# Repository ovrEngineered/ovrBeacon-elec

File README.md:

# ovrBeacon-elec

This project contains an open-source implementation of a Bluetooth Low Energy sensor beacon.
The beacon has the following features:
 - Integrated temperature sensor
 - Integrated light sensor
 - Integrated accelerometer
 - Remotely controlled LEDs
 - Wireless charging via Qi standard
 
Note: this repository contains the schematics and PCB design. The firmware repository is located [here](https://github.com/ovrEngineered/ovrBeacon-fw).

## Physical Description

| Height       | Width        | Depth w/ programming header | Depth w/o programming header |
| ------------ | ------------ | --------------------------- | ---------------------------- |
| 1.85" (47mm) | 1.06" (27mm) | 0.57" (14.48mm)             | 0.41" (10.41mm)              |

## Parameters
| Parameter               | Min  | Typical | Max    | Units |
| ----------------------- | ---- | ------- | ------ | ----- |
| Temperature accuracy**  | -    | +/- 1   | -      | °C    |
| Acceleration range      | -16  | -       | +16    | g     |
| Acceleration resolution | -    | 4       | -      | mg    |
| Light sensitivity       | 0.01 | -       | 64,000 | lux   |
| Battery Capacity***     | -    | 500     | -      | mAh.  |
** accuracy can be increased with pin-compatible parts 

*** capacity can be increased with replacement batteries

## Links
 * [Schematic PDF](output/ovrBeacon_schematic.pdf)
 * [PCB Layout PDF](output/ovrBeacon_layout.pdf)

## Built With
 * [KiCad](http://kicad-pcb.org/)

## Versioning
We use [SemVer](http://semver.org/) for versioning. For the versions available, see the [tags on this repository](https://github.com/ovrEngineered/ovrBeacon-elec/tags). 

## License
This project is licensed under the MIT License:

> Permission is hereby granted, free of charge, to any person obtaining a copy of this software and associated documentation files (the "Software"), to deal in the Software without restriction, including without limitation the rights to use, copy, modify, merge, publish, distribute, sublicense, and/or sell copies of the Software, and to permit persons to whom the Software is furnished to do so, subject to the following conditions:
>
> The above copyright notice and this permission notice shall be included in all copies or substantial portions of the Software.
>
> THE SOFTWARE IS PROVIDED "AS IS", WITHOUT WARRANTY OF ANY KIND, EXPRESS OR IMPLIED, INCLUDING BUT NOT LIMITED TO THE WARRANTIES OF MERCHANTABILITY, FITNESS FOR A PARTICULAR PURPOSE AND NONINFRINGEMENT. IN NO EVENT SHALL THE AUTHORS OR COPYRIGHT HOLDERS BE LIABLE FOR ANY CLAIM, DAMAGES OR OTHER LIABILITY, WHETHER IN AN ACTION OF CONTRACT, TORT OR OTHERWISE, ARISING FROM, OUT OF OR IN CONNECTION WITH THE SOFTWARE OR THE USE OR OTHER DEALINGS IN THE SOFTWARE.

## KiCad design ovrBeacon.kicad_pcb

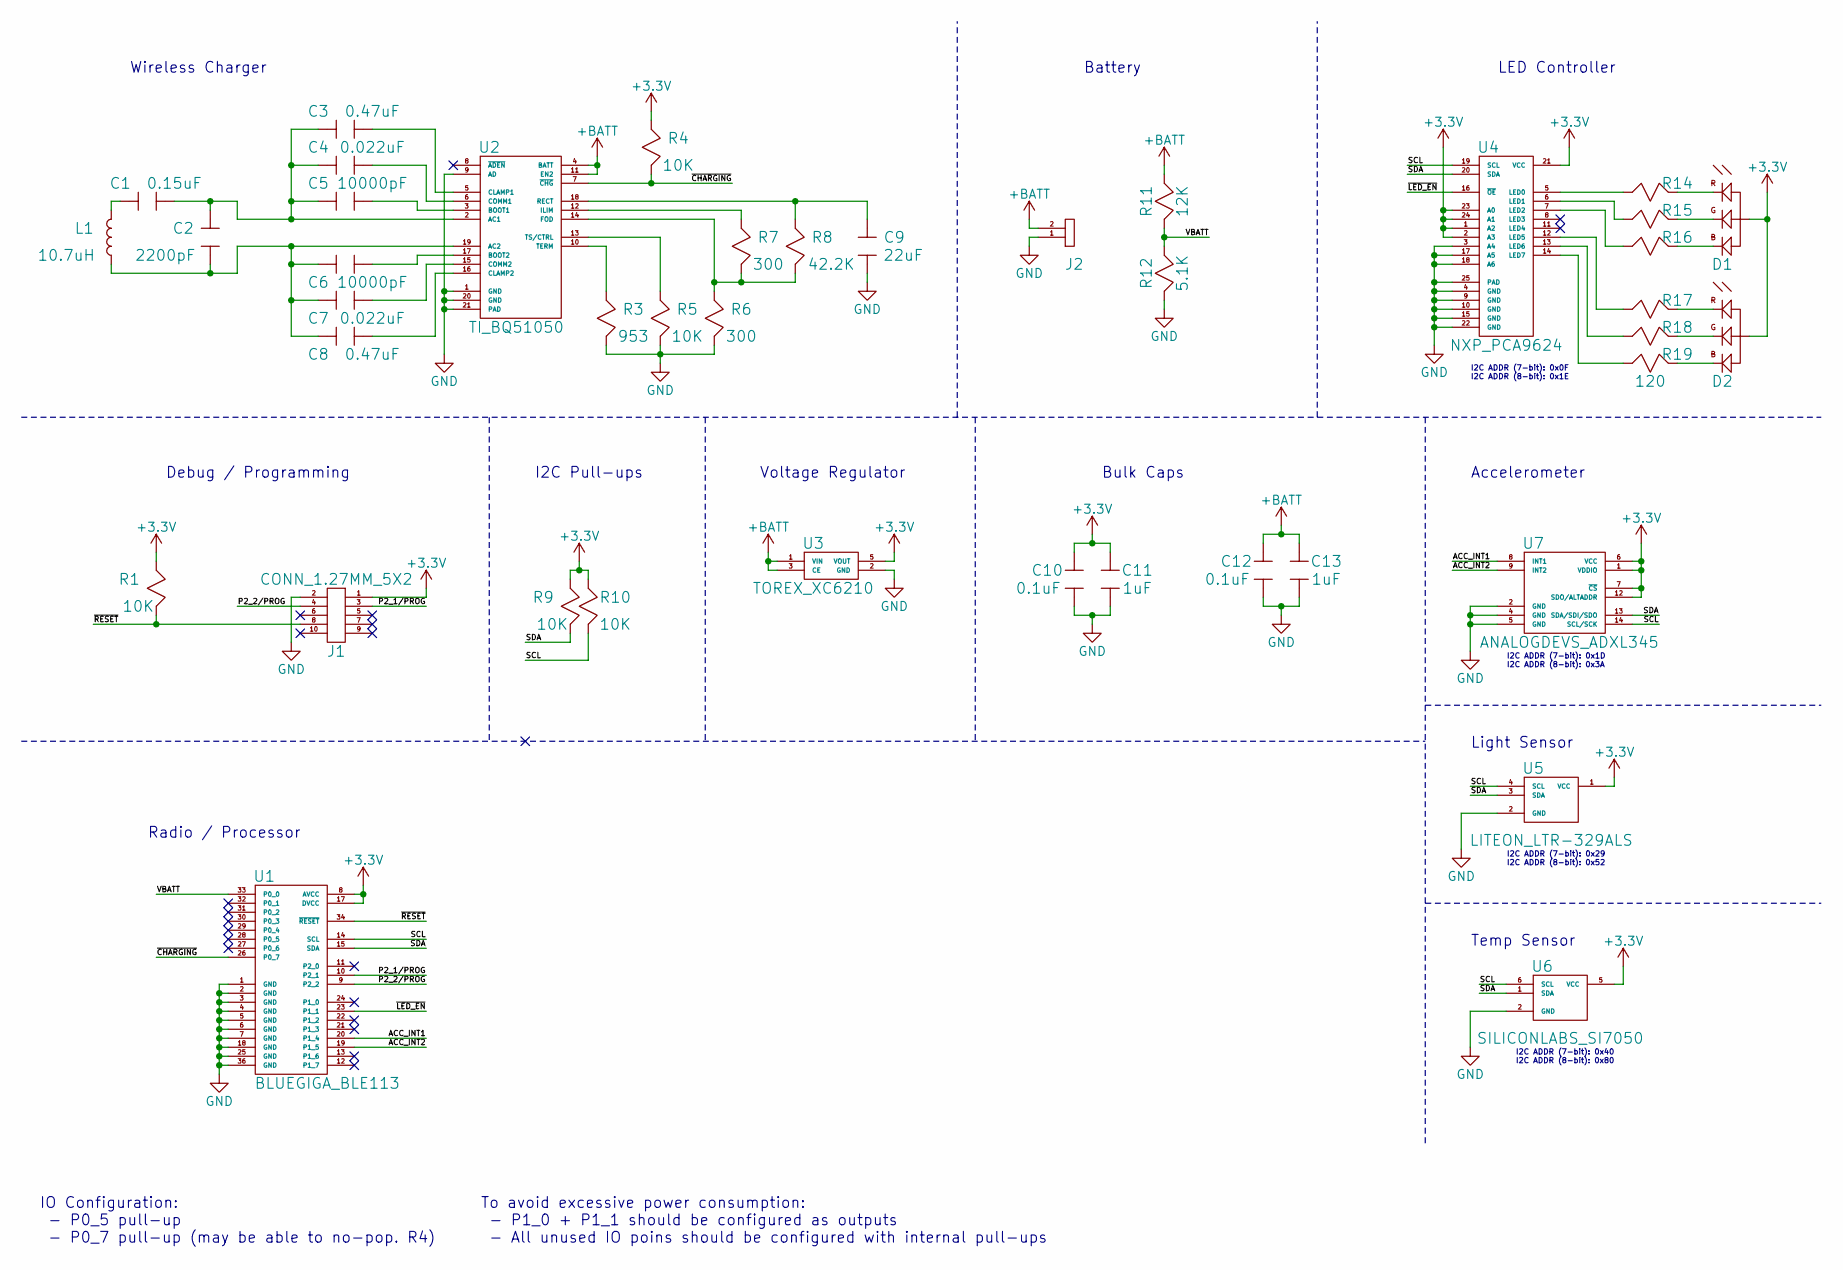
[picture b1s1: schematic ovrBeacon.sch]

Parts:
C1: C_0.15uF_25v_0603; C_0603; Man. Part Num. C1608X7R1E154K080AA
C2: C_2200pF_50v_0603; C_0603; Man. Part Num. GRM188R71H222KA01D
C3, C8: C_0.47uF_25v_0603; C_0603; Man. Part Num. C1608X5R1E474K080AC
C4, C7: C_0.022uF_25v_0603; C_0603; Man. Part Num. GRM188R71E223KA01D
C5, C6: C_10000pF_25v_0603; C_0603; Man. Part Num. GRM188R71E103KA01D
C9: C_22uF_25v_0805; C_0805; Man. Part Num. GRT21BR61E226ME13L
C10, C12: C_0.1uF_10v_0603; C_0603; Man. Part Num. GRM188R71C104KA01D
C11, C13: C_1uF_10v_0805; C_0805; Man. Part Num. GRM21BR71A105KA01L
D1, D2: CREE_CLV1A_FKB; Man. Part Num. CLV1A-FKB-CK1N1G1BB7R4S3
J1: CONN_1.27MM_5X2; 20021111-00010T4LF; Man. Part Num. 20021111-00010T4LF
J2: CONN_2MM_2; SIP_2MM_2; Man. Part Num. 951102-8622-AR
L1: QIRX_10.7uH; SIP_2MM_2; Man. Part Num. IWAS3827ECEB100J50
R1, R4, R5, R9, R10: R_10K_1%_0603; R_0603; Man. Part Num. CRCW060310K0FKEA
R3: R_953_1%_0603; R_0603; Man. Part Num. RC0603FR-07953RL
R6, R7: R_300_1%_0603; R_0603; Man. Part Num. RC0603FR-07300RL
R8: R_42.2K_1%_0603; R_0603; Man. Part Num. RC0603FR-0742K2L
R11: R_12K_1%_0603; R_0603; Man. Part Num. CRCW060312K0FKEA
R12: R_5.1K_1%_0603; R_0603; Man. Part Num. CRCW06035K10FKEA
R14, R15, R16, R17, R18, R19: R_120_1%_0603; R_0603; Man. Part Num. CRCW0603120RFKEA
U1: BLUEGIGA_BLE113; BLE113; Man. Part Num. BLE113-A-M256K
U2: TI_BQ51050; Man. Part Num. BQ51050BRHLR
U3: TOREX_XC6210; SOT-25-5; Man. Part Num. XC6210B332MR-G
U4: NXP_PCA9624; Man. Part Num. PCA9624BS,118
U5: LITEON_LTR-329ALS; Man. Part Num. LTR-329ALS-01
U6: SILICONLABS_SI7050; Man. Part Num. SI7050-A20-IM
U7: ANALOGDEVS_ADXL345; Man. Part Num. ADXL345BCCZ-RL

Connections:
+3V3: C10.1, C11.1, D1.2 (ANODE), D2.2 (ANODE), J1.1, R1.1, R4.1, R9.1, R10.1, U1.8 (AVCC), U1.17 (DVCC), U3.5 (VOUT), U4.1 (A2), U4.2 (A3), U4.21 (VCC), U4.23 (A0), U4.24 (A1), U5.1 (VCC), U6.5 (VCC), U7.1 (VDDIO), U7.6 (VCC), U7.7 (~CS), U7.12 (SDO/ALTADDR)
+BATT: C12.1, C13.1, J2.2, R11.1, U2.4 (BATT), U2.11 (EN2), U3.1 (VIN), U3.3 (CE)
/ACC_INT1: U1.20 (P1_4), U7.8 (INT1)
/ACC_INT2: U1.19 (P1_5), U7.9 (INT2)
/P2_1/PROG: J1.3, U1.10 (P2_1)
/P2_2/PROG: J1.4, U1.9 (P2_2)
/SCL: R10.2, U1.14 (SCL), U4.19 (SCL), U5.4 (SCL), U6.6 (SCL), U7.14 (SCL/SCK)
/SDA: R9.2, U1.15 (SDA), U4.20 (SDA), U5.3 (SDA), U6.1 (SDA), U7.13 (SDA/SDI/SDO)
/VBATT: R11.2, R12.1, U1.33 (P0_0)
/~CHARGING: R4.2, U1.26 (P0_7), U2.7 (~CHG)
/~LED_EN: U1.23 (P1_1), U4.16 (~OE)
/~RESET: J1.8, R1.2, U1.34 (~RESET)
GND: C9.2, C10.2, C11.2, C12.2, C13.2, J1.2, J2.1, R3.2, R5.2, R6.2, R12.2, U1.1 (GND), U1.2 (GND), U1.3 (GND), U1.4 (GND), U1.5 (GND), U1.6 (GND), U1.7 (GND), U1.18 (GND), U1.25 (GND), U1.36 (GND), U2.1 (GND), U2.9 (AD), U2.20 (GND), U2.21 (PAD), U3.2 (GND), U4.3 (A4), U4.4 (GND), U4.9 (GND), U4.10 (GND), U4.15 (GND), U4.17 (A5), U4.18 (A6), U4.22 (GND), U4.25 (PAD), U5.2 (GND), U6.2 (GND), U7.2 (GND), U7.4 (GND), U7.5 (GND)
unnamed: C1.1, L1.1
unnamed: C1.2, C2.1, C3.1, C4.1, C5.1, U2.2 (AC1)
unnamed: C2.2, C6.1, C7.1, C8.1, L1.2, U2.19 (AC2)
unnamed: C3.2, U2.5 (CLAMP1)
unnamed: C4.2, U2.6 (COMM1)
unnamed: C5.2, U2.3 (BOOT1)
unnamed: C6.2, U2.17 (BOOT2)
unnamed: C7.2, U2.15 (COMM2)
unnamed: C8.2, U2.16 (CLAMP2)
unnamed: C9.1, R8.1, U2.18 (RECT)
unnamed: D1.1 (CATHODE_RED), R14.2
unnamed: D1.3 (CATHODE_BLUE), R16.2
unnamed: D1.4 (CATHOD_GREEN), R15.2
unnamed: D2.1 (CATHODE_RED), R17.2
unnamed: D2.3 (CATHODE_BLUE), R19.2
unnamed: D2.4 (CATHOD_GREEN), R18.2
unnamed: R3.1, U2.10 (TERM)
unnamed: R5.1, U2.13 (TS/CTRL)
unnamed: R6.1, R7.1, R8.2, U2.14 (FOD)
unnamed: R7.2, U2.12 (ILIM)
unnamed: R14.1, U4.5 (LED0)
unnamed: R15.1, U4.6 (LED1)
unnamed: R16.1, U4.7 (LED2)
unnamed: R17.1, U4.12 (LED5)
unnamed: R18.1, U4.13 (LED6)
unnamed: R19.1, U4.14 (LED7)

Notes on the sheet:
Debug / Programming
Radio / Processor
I2C ADDR (7-bit): 0x29 I2C ADDR (8-bit): 0x52
I2C ADDR (7-bit): 0x40 I2C ADDR (8-bit): 0x80
I2C ADDR (7-bit): 0x1D I2C ADDR (8-bit): 0x3A
I2C ADDR (7-bit): 0x0F I2C ADDR (8-bit): 0x1E
I2C Pull-ups
Wireless Charger
Battery
LED Controller
Accelerometer
Light Sensor
Temp Sensor
Voltage Regulator
Bulk Caps
To avoid excessive power consumption: - P1_0 + P1_1 should be configured as outputs - All unused IO poins should be configured with internal pull-ups
IO Configuration: - P0_5 pull-up - P0_7 pull-up (may be able to no-pop. R4)

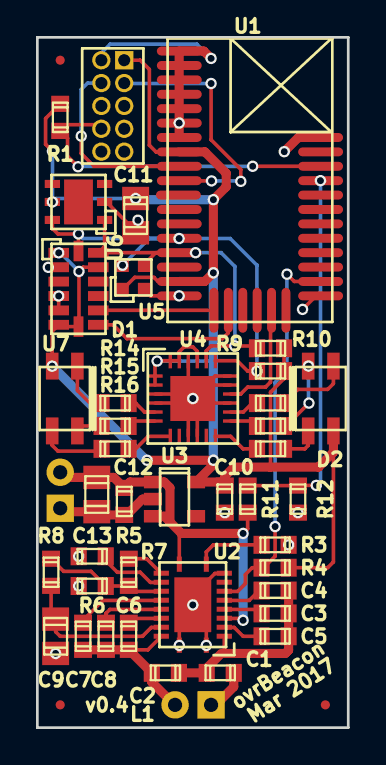
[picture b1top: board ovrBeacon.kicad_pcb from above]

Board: 2 copper layers, 17.3 x 38.4 mm, 45 parts (0 on the bottom side), 39 nets.

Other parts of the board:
FID1, FID2, FID3: fiducial

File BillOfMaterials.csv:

Reference,Value,Footprint,Datasheet,Manufacturer,Man. Part Num.,Supplier,Supplier Part Num.,Comp. Value,Quantity
U1,BLUEGIGA_BLE113,ovrEngineered:BLE113,http://media.digikey.com/pdf/Data%20Sheets/BlueGiga%20PDFs/B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,BlueGiga,BLE113-A-M256K,Digi-Key,1446-1035-1-ND,,1
R1 R5 R4 R9 R10,R_10K_1%_0603,ovrEngineered:R_0603,http://www.vishay.com/docs/20035/dcrcwe3.pdf,Vishay_Dale,CRCW060310K0FKEA,Digi-Key,541-10.0KHCT-ND,10K,5
R2,R_0_0603,ovrEngineered:R_0603,http://www.vishay.com/docs/20035/dcrcwe3.pdf,Vishay_Dale,CRCW06030000Z0EA,Digi-Key,541-0.0GCT-ND,0,1
C1,C_0.15uF_25v_0603,ovrEngineered:C_0603,http://www.tdk.com/pdf/TDKMLCCCapRange.pdf,TDK Corporation,C1608X7R1E154K080AA,Digi-Key,445-5190-1-ND,0.15uF,1
C2,C_2200pF_50v_0603,ovrEngineered:C_0603,http://search.murata.co.jp/Ceramy/image/img/A01X/G101/ENG/GR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,Murata,GRM188R71H222KA01D,Digi-Key,"	490-1500-1-ND",2200pF,1
C6 C5,C_10000pF_25v_0603,ovrEngineered:C_0603,http://search.murata.co.jp/Ceramy/image/img/A01X/partnumberi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,Murata,GRM188R71E103KA01D,Digi-Key,490-1520-1-ND,10000pF,2
C3 C8,C_0.47uF_25v_0603,ovrEngineered:C_0603,http://www.tdk.com/pdf/TDKMLCCCapRange.pdf,TDK Corporation,C1608X5R1E474K080AC,Digi-Key,445-5144-1-ND,0.47uF,2
C4 C7,C_0.022uF_25v_0603,ovrEngineered:C_0603,http://search.murata.co.jp/Ceramy/image/img/A01X/G101/ENG/GR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,Murata,GRM188R71E223KA01D,Digi-Key,490-9761-1-ND,0.022uF,2
C9,C_22uF_25v_0805,ovrEngineered:C_0805,http://search.murata.co.jp/Ceramy/image/img/A01X/G101/ENG/GR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,Murata,GRT21BR61E226ME13L,Digi-Key,490-12389-1-ND,22uF,1
R8,R_42.2K_1%_0603,ovrEngineered:R_0603,http://www.yageo.com/exep/pages/download/literatures/PYu-R_M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,Yageo,RC0603FR-0742K2L,Digi-Key,311-42.2KHRCT-ND,42.2K,1
R6 R7,R_300_1%_0603,ovrEngineered:R_0603,http://www.yageo.com/NewPortal/yageodocoutput?fileName=/pdf/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,Yageo,RC0603FR-07300RL,Digi-Key,311-300HRCT-ND,300,2
R3,R_953_1%_0603,ovrEngineered:R_0603,http://www.yageo.com.tw/exep/pages/download/literatures/PYu-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,Yageo,RC0603FR-07953RL,Digi-Key,311-953HRCT-ND,953,1
C13 C11,C_1uF_10v_0805,ovrEngineered:C_0805,http://psearch.murata.com/capacitor/product/GRM21BR71A106KE5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,Murata,GRM21BR71A105KA01L,Digi-Key,490-1695-1-ND,1uF,2
C12 C10,C_0.1uF_10v_0603,ovrEngineered:C_0603,http://search.murata.co.jp/Ceramy/image/img/A01X/G101/ENG/GR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,Murata,GRM188R71C104KA01D,Digi-Key,490-1532-1-ND,0.1uF,2
R14 R15 R16 R17 R18 R19,R_120_1%_0603,ovrEngineered:R_0603,http://www.vishay.com/docs/20035/dcrcwe3.pdf,Vishay_Dale,CRCW0603120RFKEA,Digi-Key,541-120HCT-ND,120,6
R11,R_12K_1%_0603,ovrEngineered:R_0603,http://www.vishay.com/docs/20035/dcrcwe3.pdf,Vishay_Dale,CRCW060312K0FKEA,Digi-Key,541-12.0KHCT-ND,12K,1
R12,R_5.1K_1%_0603,ovrEngineered:R_0603,http://www.vishay.com/docs/20035/dcrcwe3.pdf,Vishay_Dale,CRCW06035K10FKEA,Digi-Key,541-5.10KHCT-ND,5.1K,1
D1 D2,CREE_CLV1A_FKB,ovrEngineered:CREE_CLV1A_FKB,http://media.digikey.com/pdf/Data%20Sheets/CREE%20Power/CLV1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,Cree Inc.,CLV1A-FKB-CK1N1G1BB7R4S3,Digi-Key,CLV1A-FKB-CK1N1G1BB7R4S3CT-ND,RGB,2
J2,CONN_2MM_2,ovrEngineered:SIP_2MM_2,http://multimedia.3m.com/mws/media/438474O/3mtm-pin-strip-he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,3M,951102-8622-AR,Digi-Key,3M9321-ND,,1
L1,QIRX_10.7uH,ovrEngineered:SIP_2MM_2,http://www.vishay.com/docs/34338/iwas3827.pdf,Vishay Dale,IWAS3827ECEB100J50,Digi-Key,541-1695-ND,10.7uH,1
U2,TI_BQ51050,ovrEngineered:TI_BQ51050,http://www.ti.com/lit/ds/symlink/bq51050b.pdf,Texas Instruments,BQ51050BRHLR,Digi-Key,296-35066-1-ND,,1
U3,TOREX_XC6210,ovrEngineered:SOT-25-5,https://www.torexsemi.com/file/xc6210/XC6210.pdf,Torex Semiconductor,XC6210B332MR-G,Digi-Key,893-1075-1-ND,,1
U4,NXP_PCA9624,ovrEngineered:NXP_PCA9624,http://www.nxp.com/documents/data_sheet/PCA9624.pdf,NXP,PCA9624BS,Digi-Key,568-5304-1-ND,,1
U5,LITEON_LTR-329ALS,ovrEngineered:LITEON_LTR-329ALS,http://optoelectronics.liteon.com/upload/download/DS86-2014-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,Lite-On,LTR-329ALS-01,Digi-Key,160-2160-1-ND,,1
U7,ANALOGDEVS_ADXL345,ovrEngineered:ANALOGDEVS_ADXL345,http://www.analog.com/media/en/technical-documentation/data-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,Analog Devices,ADXL345BCCZ-RL,Digi-Key,ADXL345BCCZ-RLCT-ND,,1
J1,CONN_1.27MM_5X2,ovrEngineered:20021111-00010T4LF,http://portal.fciconnect.com/Comergent//fci/drawing/20021111.pdf,Amphenol,20021111-00010T4LF,Digi-Key,609-3712-ND,,1
U6,SILICONLABS_SI7050,,http://www.silabs.com/Support%20Documents/TechnicalDocs/Si70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,Silicon Labs,SI7050-A20-IM,Digi-Key,336-3118-5-ND,,1

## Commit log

2016-07-31 added KiCAD externals
2017-01-04 initial commit of version 0.3…passed DFM, waiting for manufacture review
2017-01-12 As manufactured
2017-02-27 Moved BOM, added pricing, added schematic and layout PDF
2017-03-07 Fixed redlines from v0.3, added fiducials for pick and place…getting ready to start adjusting component centers for pick and place
2017-03-07 Adjusted component centers and orientation for pick and place
2017-03-07 ready for fabrication w/ fiducials, redlines from v0.3, and pick and place file
2017-03-07 Updated pricing document w/ variants
2017-03-08 Added various pictures
2017-03-08 resized profile view
2017-03-08 Resized dimension view
2017-03-08 Created Readme.md
2017-03-08 Updated tags link
